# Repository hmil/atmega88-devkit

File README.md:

# Atmega88 devkit

Development kit for the Atmega88p inspired by Arduino boards.

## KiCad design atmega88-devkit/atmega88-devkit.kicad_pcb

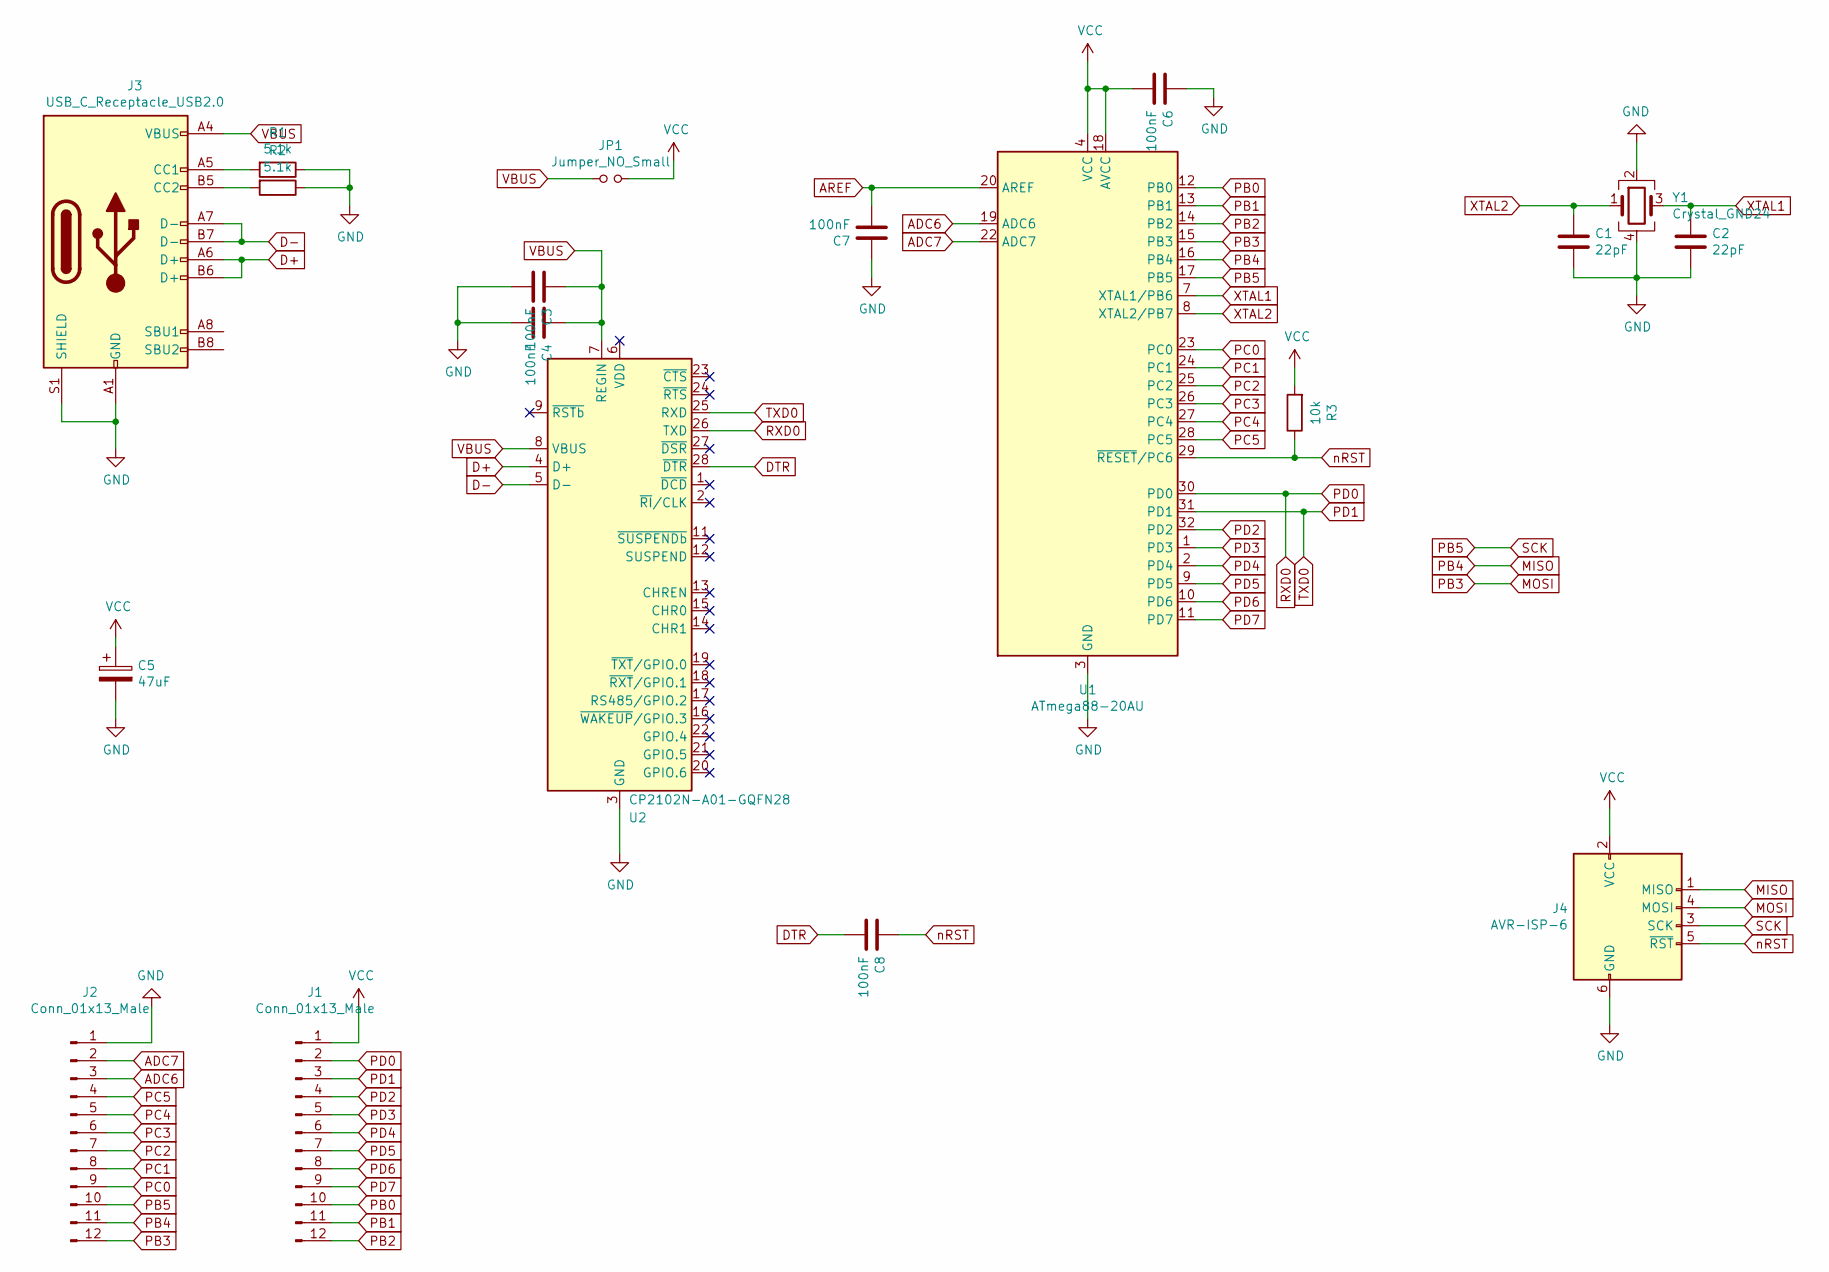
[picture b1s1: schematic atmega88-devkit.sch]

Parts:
C1, C2: 22pF; C_0603_1608Metric_Pad1.08x0.95mm_HandSolder
C3, C4, C6, C7, C8: 100nF; C_0603_1608Metric_Pad1.08x0.95mm_HandSolder
C5: 47uF; C_Elec_4x5.4
J1, J2: Conn_01x13_Male; PinHeader_1x12_P2.54mm_Vertical
J3: USB_C_Receptacle_USB2.0; USB_C_Receptacle_Palconn_UTC16-G
J4: AVR-ISP-6; Tag-Connect_TC2030-IDC-NL_2x03_P1.27mm_Vertical
JP1: Jumper_NO_Small; SolderJumper-2_P1.3mm_Open_TrianglePad1.0x1.5mm
R1, R2: 5.1k; R_0603_1608Metric_Pad0.98x0.95mm_HandSolder
R3: 10k; R_0603_1608Metric_Pad0.98x0.95mm_HandSolder
U1: ATmega88-20AU; TQFP-32_7x7mm_P0.8mm
U2: CP2102N-A01-GQFN28; QFN-28-1EP_5x5mm_P0.5mm_EP3.35x3.35mm
Y1: Crystal_GND24; Crystal_SMD_3225-4Pin_3.2x2.5mm

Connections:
ADC6: J2.3, U1.19 (ADC6)
ADC7: J2.2, U1.22 (ADC7)
AREF: C7.2, U1.20 (AREF)
D+: J3.A6 (D+), J3.B6 (D+), U2.4 (D+)
D-: J3.A7 (D-), J3.B7 (D-), U2.5 (D-)
DTR: C8.2, U2.28 (~DTR)
GND: C1.2, C2.2, C3.2, C4.2, C5.2, C6.1, C7.1, J2.1, J3.A1 (GND), J3.A12 (GND), J3.B1 (GND), J3.B12 (GND), J3.S1 (SHIELD), J4.6 (GND), R1.1, R2.1, U1.3 (GND), U1.5 (GND), U1.21 (GND), U2.3 (GND), U2.29 (GND), Y1.2, Y1.4
MISO: J2.11, J4.1 (MISO), U1.16 (PB4)
MOSI: J2.12, J4.4 (MOSI), U1.15 (PB3)
unnamed: J3.A5 (CC1), R1.2
unnamed: J3.B5 (CC2), R2.2
PB0: J1.10, U1.12 (PB0)
PB1: J1.11, U1.13 (PB1)
PB2: J1.12, U1.14 (PB2)
PB5: J2.10, J4.3 (SCK), U1.17 (PB5)
PC0: J2.9, U1.23 (PC0)
PC1: J2.8, U1.24 (PC1)
PC2: J2.7, U1.25 (PC2)
PC3: J2.6, U1.26 (PC3)
PC4: J2.5, U1.27 (PC4)
PC5: J2.4, U1.28 (PC5)
PD0: J1.2, U1.30 (PD0), U2.26 (TXD)
PD1: J1.3, U1.31 (PD1), U2.25 (RXD)
PD2: J1.4, U1.32 (PD2)
PD3: J1.5, U1.1 (PD3)
PD4: J1.6, U1.2 (PD4)
PD5: J1.7, U1.9 (PD5)
PD6: J1.8, U1.10 (PD6)
PD7: J1.9, U1.11 (PD7)
VBUS: C3.1, C4.1, J3.A4 (VBUS), J3.A9 (VBUS), J3.B4 (VBUS), J3.B9 (VBUS), JP1.1, U2.7 (REGIN), U2.8 (VBUS)
VCC: C5.1, C6.2, J1.1, J4.2 (VCC), JP1.2, R3.2, U1.4 (VCC), U1.6 (VCC), U1.18 (AVCC)
XTAL1: C2.1, U1.7 (XTAL1/PB6), Y1.3
XTAL2: C1.1, U1.8 (XTAL2/PB7), Y1.1
nRST: C8.1, J4.5 (~RST), R3.1, U1.29 (~RESET~/PC6)

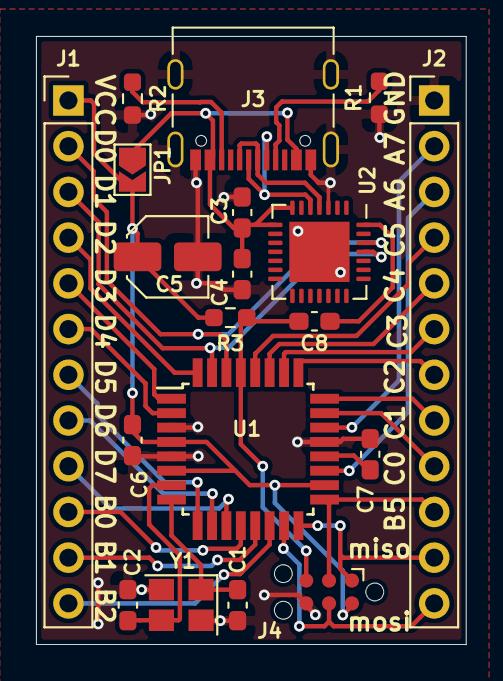
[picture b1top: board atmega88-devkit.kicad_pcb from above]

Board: 2 copper layers, 23.9 x 33.8 mm, 19 parts (0 on the bottom side), 34 nets.
